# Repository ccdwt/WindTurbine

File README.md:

This directory contains files and information related to the Calvin College Demonstration Wind Turbine.

--Matthew Kuperus Heun, 20 May 2013

Configuration should be done by editing variables in make.inc, otherwise you should just be able to invoke:

# make install

and everything should be installed

# todo
	1. add Monit to makefile 1/1 # DONE
	2. add startup scripts to install 4/4 # DONE
	3. add cron jobs to install 2/2 #DONE 
	4. add configuration to turbine, modbus, weather, db_write, and dropbox 5/5 #DONE

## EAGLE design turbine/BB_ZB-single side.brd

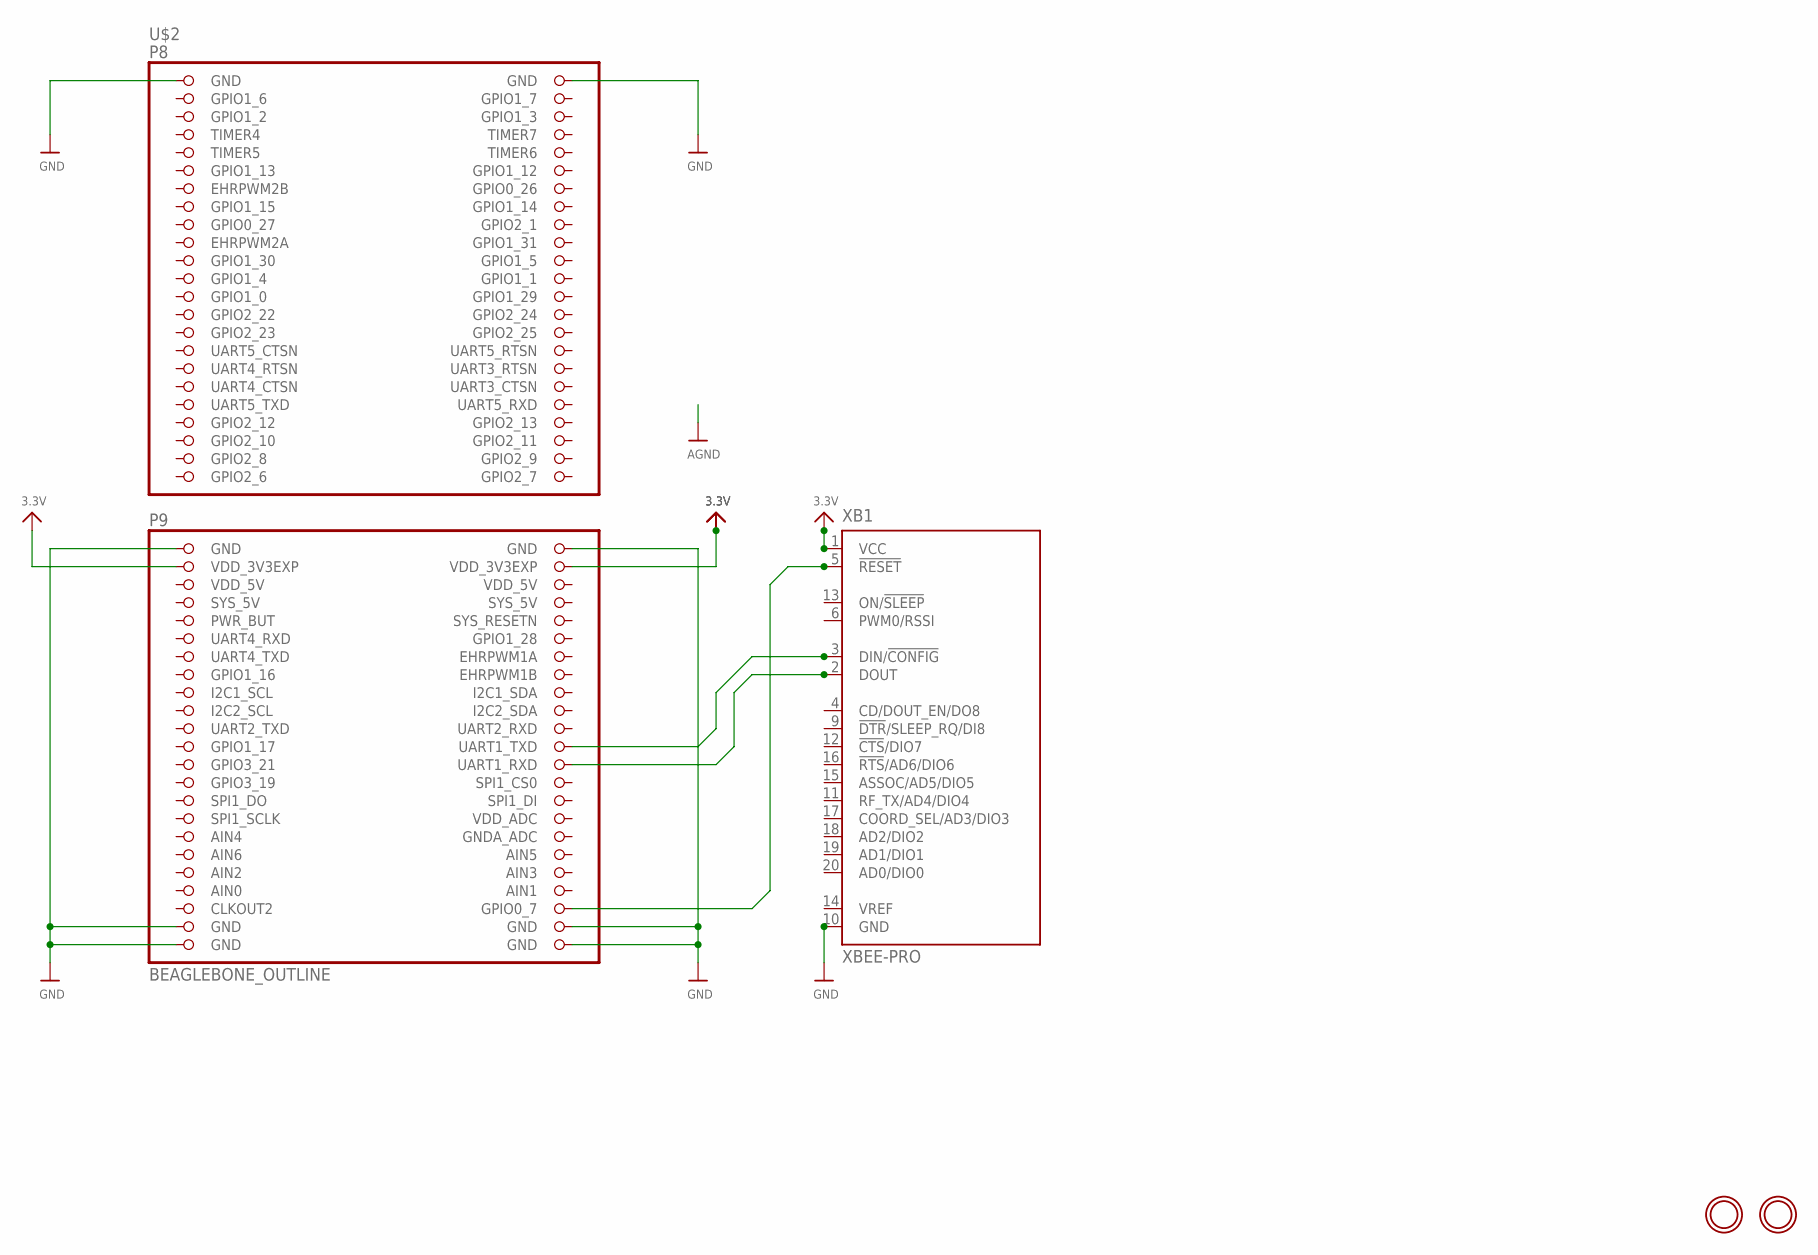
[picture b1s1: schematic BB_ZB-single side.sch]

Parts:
U$2: BEAGLEBONE_OUTLINE; BEAGLEBONE_SHIELD
U$22, U$23: MOUNTINGHOLE3.0THIN; MOUNTINGHOLE_3.0_PLATEDTHIN
XB1: XBEE-PRO

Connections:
3.3V: U$2.49 (VDD_3V3EXP), U$2.50 (VDD_3V3EXP), XB1.1 (VCC)
AIN0: U$2.85 (AIN0)
AIN3: U$2.84 (AIN3)
GND: U$2.1 (GND), U$2.2 (GND), U$2.47 (GND), U$2.48 (GND), U$2.89 (GND), U$2.90 (GND), U$2.91 (GND), U$2.92 (GND), XB1.10 (GND)
GPIO1_6: U$2.3 (GPIO1_6)
GPIO1_7: U$2.4 (GPIO1_7)
GPIO2_6: U$2.45 (GPIO2_6)
GPIO2_7: U$2.46 (GPIO2_7)
GPIO2_8: U$2.43 (GPIO2_8)
GPIO2_9: U$2.44 (GPIO2_9)
GPIO2_11: U$2.42 (GPIO2_11)
unnamed: U$2.88 (GPIO0_7), XB1.5 (!RESET)
unnamed: U$2.70 (UART1_TXD), XB1.3 (DIN/!CONFIG)
unnamed: U$2.72 (UART1_RXD), XB1.2 (DOUT)
VDD_5V: U$2.51 (VDD_5V), U$2.52 (VDD_5V)

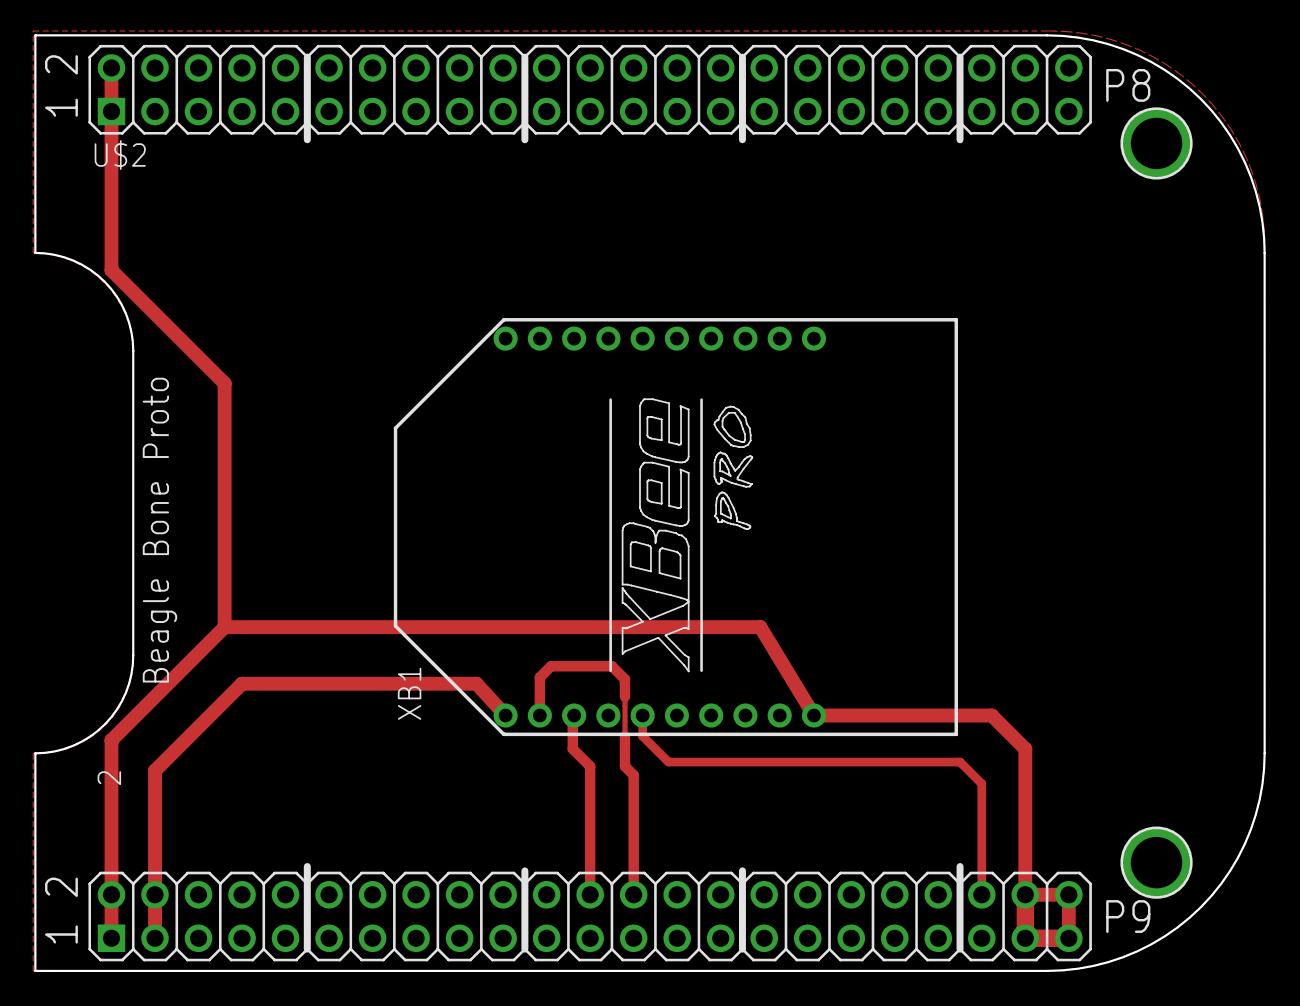
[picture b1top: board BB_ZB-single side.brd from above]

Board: 2 copper layers, 71.8 x 54.6 mm, 4 parts (0 on the bottom side), 6 nets.

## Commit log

2000-01-01 mount sd card in directory where db is stored
2013-07-02 code from old repository
2013-07-03 initial working Makefile
2013-07-03 better makefile
2013-07-10 added fixLocale.sh basically dos2unix
2013-07-10 fixed serial issues with interrupt + general cleanup
2013-07-10 fixed fixLocale.sh
2013-07-11 fixed busy wait
2013-07-11 refined the Makefile
2013-07-12 reverted to old incremental packet parsing
2013-07-12 added logfile as an argument to logger.c
2013-07-12 added logging version of weather
2013-07-12 changes to Makefile for weather/log
2013-07-16 fixed negative numbers in modbus
2013-07-16 added CCFLAGS
2013-07-16 appeared to have fixed the hanging problem with logger.c
2013-07-19 weather with segfault after bad file descriptor
2013-07-22 initial work with db
2013-07-26 Database code working for the most part
2013-07-29 made weather a daemon
2013-07-29 made logger a daemon
2013-07-29 add lockfile support
2013-07-31 Constants injection for Modbus
2013-07-31 added configuration by variables
2013-07-31 db_write configuration update
2013-08-01 Fixed daemon separation for modbus
2013-08-01 cleanup in modbus
2013-08-01 added startup scripts to modbus
2013-08-01 added configuration and cron instalation to db_write
2013-08-01 updated todo's
2013-08-01 added startup script install for weather
2013-08-01 install init script Turbine
2013-08-02 drop box Makefile and configuration
2013-08-02 dependency checking for Perl modbus
2013-08-02 dependency checking for db_write
2013-08-02 run the uart1 file from Makefile so /dev/ttyO1 exists right away
2013-08-02 better way to run cpan from modbus Makefile
2013-08-02 cleanup
2013-08-02 fixed small problem in makefile
2013-08-02 fixed syntax error in makefile
2013-08-02 WIP monit added
2013-08-05 fixed monitrc configuring
2013-08-05 Makefile: added clean target for all subdirs
2013-08-05 configurable monitrc file
2013-08-05 added code so that db_write kills stuck instances
2013-08-05 updated todos
2013-08-05 final commit before moving to final locations
2013-08-05 changed config file name
2013-08-05 cleanup and config fixes
2013-08-05 fixed error in makefile
2013-08-06 final commit
2013-08-08 aparently all fixed for direct install
2013-08-08 couple of tweaks
2013-08-08 more tweaks
2013-08-09 removed unneeded dependency
2013-08-09 fixed cpan autoconf problem
2013-08-09 fixed problem with modbus makefile
2013-08-12 allow device connected by usb for monit
2013-08-15 got rid of CPAN configuration
2013-08-15 multiple small fixes
2013-08-15 fixed python syntax errors
2013-08-15 fixed dependency check
2013-08-16 working copy
2013-08-19 fixed https problem
2013-08-19 fixed needless opkg install
2013-08-19 undo last commit
2013-08-23 initial data output for web
2013-08-23 better data object
2013-08-23 fixed some of the values I store
2013-08-28 added web interface
2013-08-28 added timeout so db_write will not hang in the case where external hosting goes down
2013-08-29 website refinements
2013-09-19 fixed error in startup script that didn't stop the processes when stop was called
2013-09-19 added Matt and Chuck to monit Email List
2013-11-07 fixed db filename
2013-11-07 couple of updates related to change of database name from test.db to windData.sqlite
2014-02-14 should fix issue where IOS isn't seeing the background
2014-02-17 fixed monitrc DB_NAME.
2014-03-10 Added profiles
    Backup profiles added from old computer.
